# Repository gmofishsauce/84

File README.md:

# Aspirational

**Everything in this repo is aspirational. Nothing has been implemented.**

# Licensing

<br />The content of this repository is licensed under a <a rel="license" href="http://creativecommons.org/licenses/by/4.0/">Creative Commons Attribution 4.0 International License</a>.

# 84CP series

84CP is a series of hardware components for student, experimenter, and hobbyist use. 84CP components are packaged on 3.1" x 1.0" breakout "surfboards". Each component has 60 pins on 0.9" centers with 0.1" traditional (not metric) spacing, allowing one component in a standard 30-pin "small" solderless breadboard or two components in a 64-pin "large" breadboard with one row of breadboard holes open on each side of the component.

The components implement 16-bit slices and include an ALU, 16-bit wide 2:1 multiplexer, registers, controls, random logic, system clock, a VGA adapter, and nonvolatile RAM. 84CP components operate from a 3.3 volt supply, but wide level shifter components are also provided for interfacing with 5 volt logic. All components are designed for use at clock rates up to 10MHz.

Logic components are specializations of AMD Xilinx XC9572XL ("9572") Complex Programmable Logic Device ("CPLD"). A characteristic of CPLDs is that the assignment of functions to pins on the device is performed by the synthesize software, usually leading to arbitrary scrambling of inputs, outputs, control lines, power, and ground. 84CP-series surfboards physically descramble the device pins. Inputs, outputs, and control lines are meaningfully grouped with power and ground at the corners.

The 84CP series is intended for hobbyiest and educational use. All 60 pins protrude upward through the board, making them easily accessible to instrumentation (oscilloscopes and logic analyzers) for debugging and educational use. The pins also allow a single wire wrap directly to the board. Below the board, the pins are long enough for solderless breadboard insertion. Each component includes a top-mount JTAG connector, allowing it to be programmed or reprogrammed at will.

# Planned 84CP series components

- 84CP01 Scrambled baseboard
- 84CP02 Descrambled combinational baseboard with 2 x 16 input, 16 bit output, four control lines, and no clock
- 84CP03 Descrambled clocked baseboard with 16 bit input, 16 bit 3-state output, and multiple control lines
- 84CP04 Descrambled clocked baseboard with 16 bit input, 16 bit output, 16 bit 3-state output, and limited control lines
- 84CP09 Baseboard with 40 MHz clock module and 4-phase 10MHz outputs
- 84CP10 24-bit level shifter with 3 lower-voltage 8-bit enables
- 84CP11 24-bit level shifter with 2 higher-voltage 8-bit enables and 6 always-enabled
- 84CP41 16-bit register unit with 3 registers and five small constants (84CP03 baseboard)
- 84CP42 16 bit register with both 3-state and regular outputs (84CP04 baseboard)
- 84CP71 Four-function ALU with adder (84CP02 baseboard)
- 84CP72 Four-function ALU with subtracter (84CP02 baseboard)
- 84CP73 16 bit 2:1 multiplexer with shifter (84CP02 baseboard)
- 84CP74 ALU flags register and associated logic (similar to 84CP04 baseboard)
- 84CP81 2M x 16 bit nonvolatile static RAM (nonstandard baseboard)
- 84CP91 10MHz 4-phase system clock with 800x600 monochrome VGA adapter (84CP09 baseboard)

# Example 84CP01 Baseboard

# Is the 9572 CPLD obsolete?

The 9572 is a programmable device with up to 72 bits of register storage and more than 1500 equivalent logic gates, not of all which can be used in practice for any particular design. It's available in 44-pin, 64-pin, and 100-pin surface mount packages.

At the cutting edge, CPLD-type devices have been superceded by Field Programmable Gate Arrays (FPGAs) containing enormous amounts of storage and uncommitted logic. Manufacturers prefer to sell denser chips with higher margins, so Xilinx (now AMD Xilinx) has been making efforts to push customers away from the 9572 and its programming software, ISE, for almost a decade.

For a variety of reasons, there has been signficant customer pushback on their efforts.

- CPLDs are signficantly simpler than FPGAs. They had found their way into numerous university engineering programs and are widely used by hobbyists.
- CPLDs use first-generation surface-mount packages like TSOP. Most FPGAs, with their very high external connection counts, are packaged in ball grid and similar packages that are difficult to work with by hand.
- CPLDs are much less expensive than FPGAs. A single 9572 is sufficient to encapsulate many simple logic designs or the entire I/O logic of a fairly complex embedded controller.
- Manufacturers are particularly hesitant to end-of-life programmable components for fear of scaring low- and medium-volume users away from their use in future designs. AMD Xilinx, for example, publicly states that its current FPGA components (such as the Spartan series) will not be end-of-lifed until at least 2035.

No end of life announcement for the 9572 has been made and it's available from all large electronics distributers from under $10 US.

But the second (and mandatory) ingredient of any programmable device is the programming software. Despite some efforts in the open source community, Xilinx' proprietary ISE software remains the only full-function solution for the 9572. The ISE programming software is no longer maintained; Xilinx has moved all development to its Vivado software, which does not support the 9572. This is a completely understandable business decision given the enormous complexity of such software.

During the 20-teens, Xilinx stopped providing ISE upgrades for recent versions of Windows and crippled the Linux version of the software. Xilinx' efforts to push customers away from CPLDs have led to a huge amount of misinformation on the internet. Another result was significant customer pushback, which eventually caused them to quietly back off from their position.

Eventually, Xilinx released a fully-functional version of the ISE software in a Linux virtual machine. The VM can be used with Oracle VirtualBox, which runs the VM and its now-obsolete version of Linux on a host network that is completely disconnected from the internet. This makes it, in my opinion, reasonably safe for use on a NATted LAN.

So that's the bottom line. The part exists and is still being manufactured. The software exists in a fully-encapsulated and isolated form. It's enough for me, as a hobbyiest, to move on with the part.

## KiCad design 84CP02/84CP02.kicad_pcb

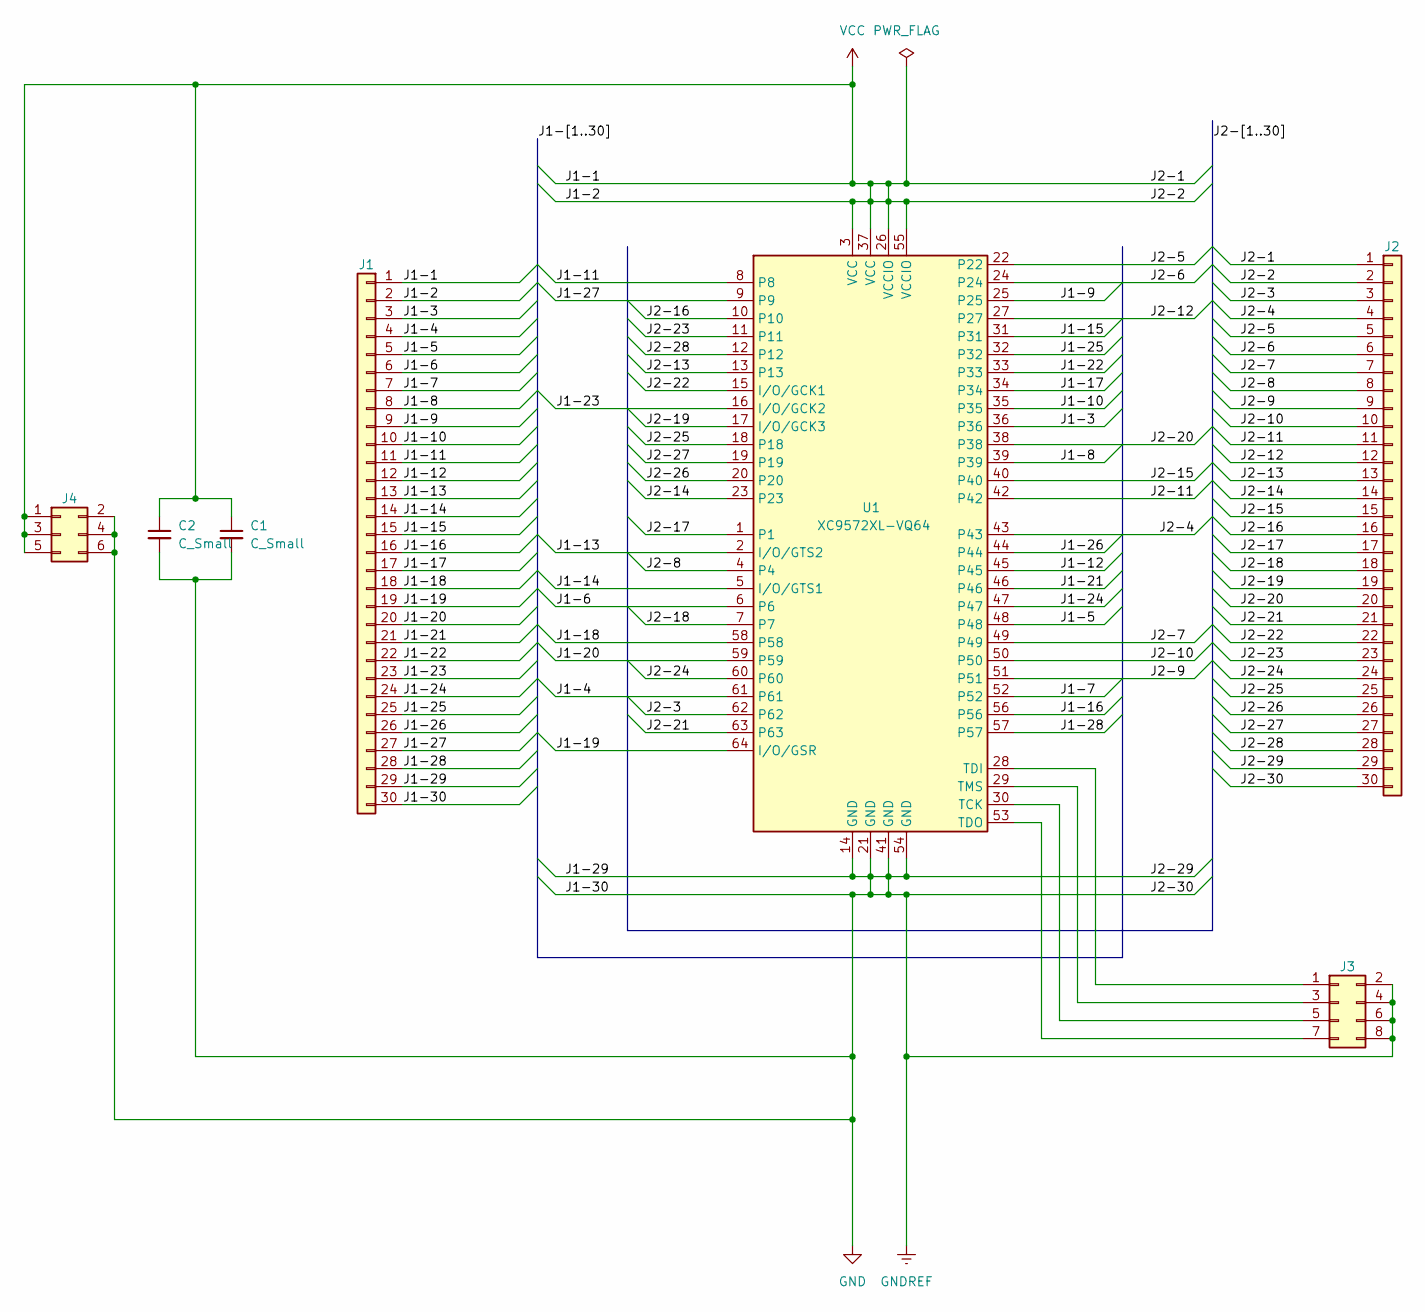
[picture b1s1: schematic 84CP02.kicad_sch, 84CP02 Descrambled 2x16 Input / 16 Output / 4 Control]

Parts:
C1, C2: C_Small; C_0805_2012Metric_Pad1.18x1.45mm_HandSolder
J1, J2: Conn_01x30; PinHeader_1x30_P2.54mm_Vertical
J3: Conn_02x05_Odd_Even; PinHeader_2x04_P2.54mm_Vertical
J4: Conn_02x03_Odd_Even; PinHeader_2x03_P2.54mm_Vertical
U1: XC9572XL-VQ64; TQFP-64_10x10mm_P0.5mm

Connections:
/J1-3: J1.3, U1.36
/J1-4: J1.4, U1.61
/J1-5: J1.5, U1.48
/J1-6: J1.6, U1.6
/J1-7: J1.7, U1.52
/J1-8: J1.8, U1.39
/J1-9: J1.9, U1.25
/J1-10: J1.10, U1.35
/J1-11: J1.11, U1.8
/J1-12: J1.12, U1.45
/J1-13: J1.13, U1.2 (I/O/GTS2)
/J1-14: J1.14, U1.5 (I/O/GTS1)
/J1-15: J1.15, U1.31
/J1-16: J1.16, U1.56
/J1-17: J1.17, U1.34
/J1-18: J1.18, U1.58
/J1-19: J1.19, U1.64 (I/O/GSR)
/J1-20: J1.20, U1.59
/J1-21: J1.21, U1.46
/J1-22: J1.22, U1.33
/J1-23: J1.23, U1.16 (I/O/GCK2)
/J1-24: J1.24, U1.47
/J1-25: J1.25, U1.32
/J1-26: J1.26, U1.44
/J1-27: J1.27, U1.9
/J1-28: J1.28, U1.57
/J2-3: J2.3, U1.62
/J2-4: J2.4, U1.43
/J2-5: J2.5, U1.22
/J2-6: J2.6, U1.24
/J2-7: J2.7, U1.49
/J2-8: J2.8, U1.4
/J2-9: J2.9, U1.51
/J2-10: J2.10, U1.50
/J2-11: J2.11, U1.42
/J2-12: J2.12, U1.27
/J2-13: J2.13, U1.13
/J2-14: J2.14, U1.23
/J2-15: J2.15, U1.40
/J2-16: J2.16, U1.10
/J2-17: J2.17, U1.1
/J2-18: J2.18, U1.7
/J2-19: J2.19, U1.17 (I/O/GCK3)
/J2-20: J2.20, U1.38
/J2-21: J2.21, U1.63
/J2-22: J2.22, U1.15 (I/O/GCK1)
/J2-23: J2.23, U1.11
/J2-24: J2.24, U1.60
/J2-25: J2.25, U1.18
/J2-26: J2.26, U1.20
/J2-27: J2.27, U1.19
/J2-28: J2.28, U1.12
GND: C1.2, C2.2, J1.29, J1.30, J2.29, J2.30, J3.2, J3.4, J3.6, J3.8, J4.2, J4.4, J4.6, U1.14 (GND), U1.21 (GND), U1.41 (GND), U1.54 (GND)
unnamed: J3.1, U1.28 (TDI)
unnamed: J3.3, U1.29 (TMS)
unnamed: J3.5, U1.30 (TCK)
unnamed: J3.7, U1.53 (TDO)
VCC: C1.1, C2.1, J1.1, J1.2, J2.1, J2.2, J4.1, J4.3, J4.5, U1.3 (VCC), U1.26 (VCCIO), U1.37 (VCC), U1.55 (VCCIO)

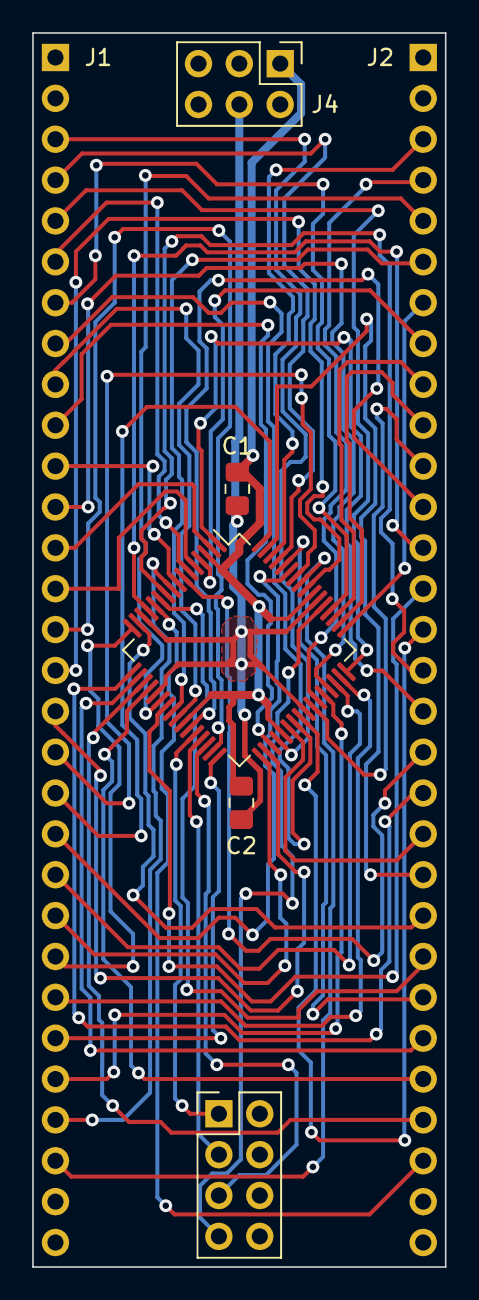
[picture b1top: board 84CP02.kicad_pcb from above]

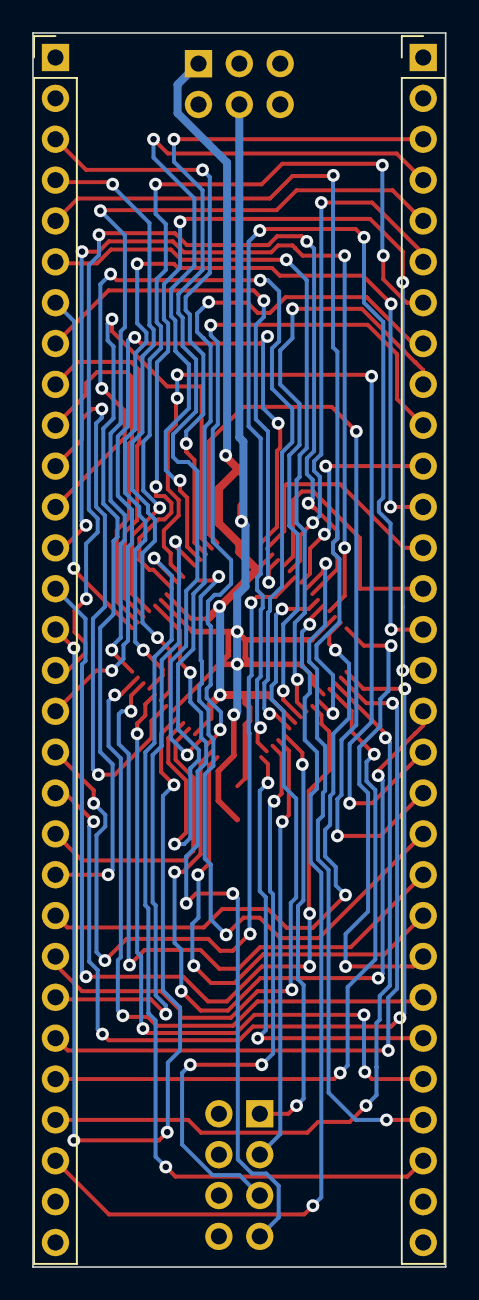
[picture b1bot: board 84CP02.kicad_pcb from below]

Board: 4 copper layers, 25.7 x 76.7 mm, 7 parts (2 on the bottom side), 58 nets.

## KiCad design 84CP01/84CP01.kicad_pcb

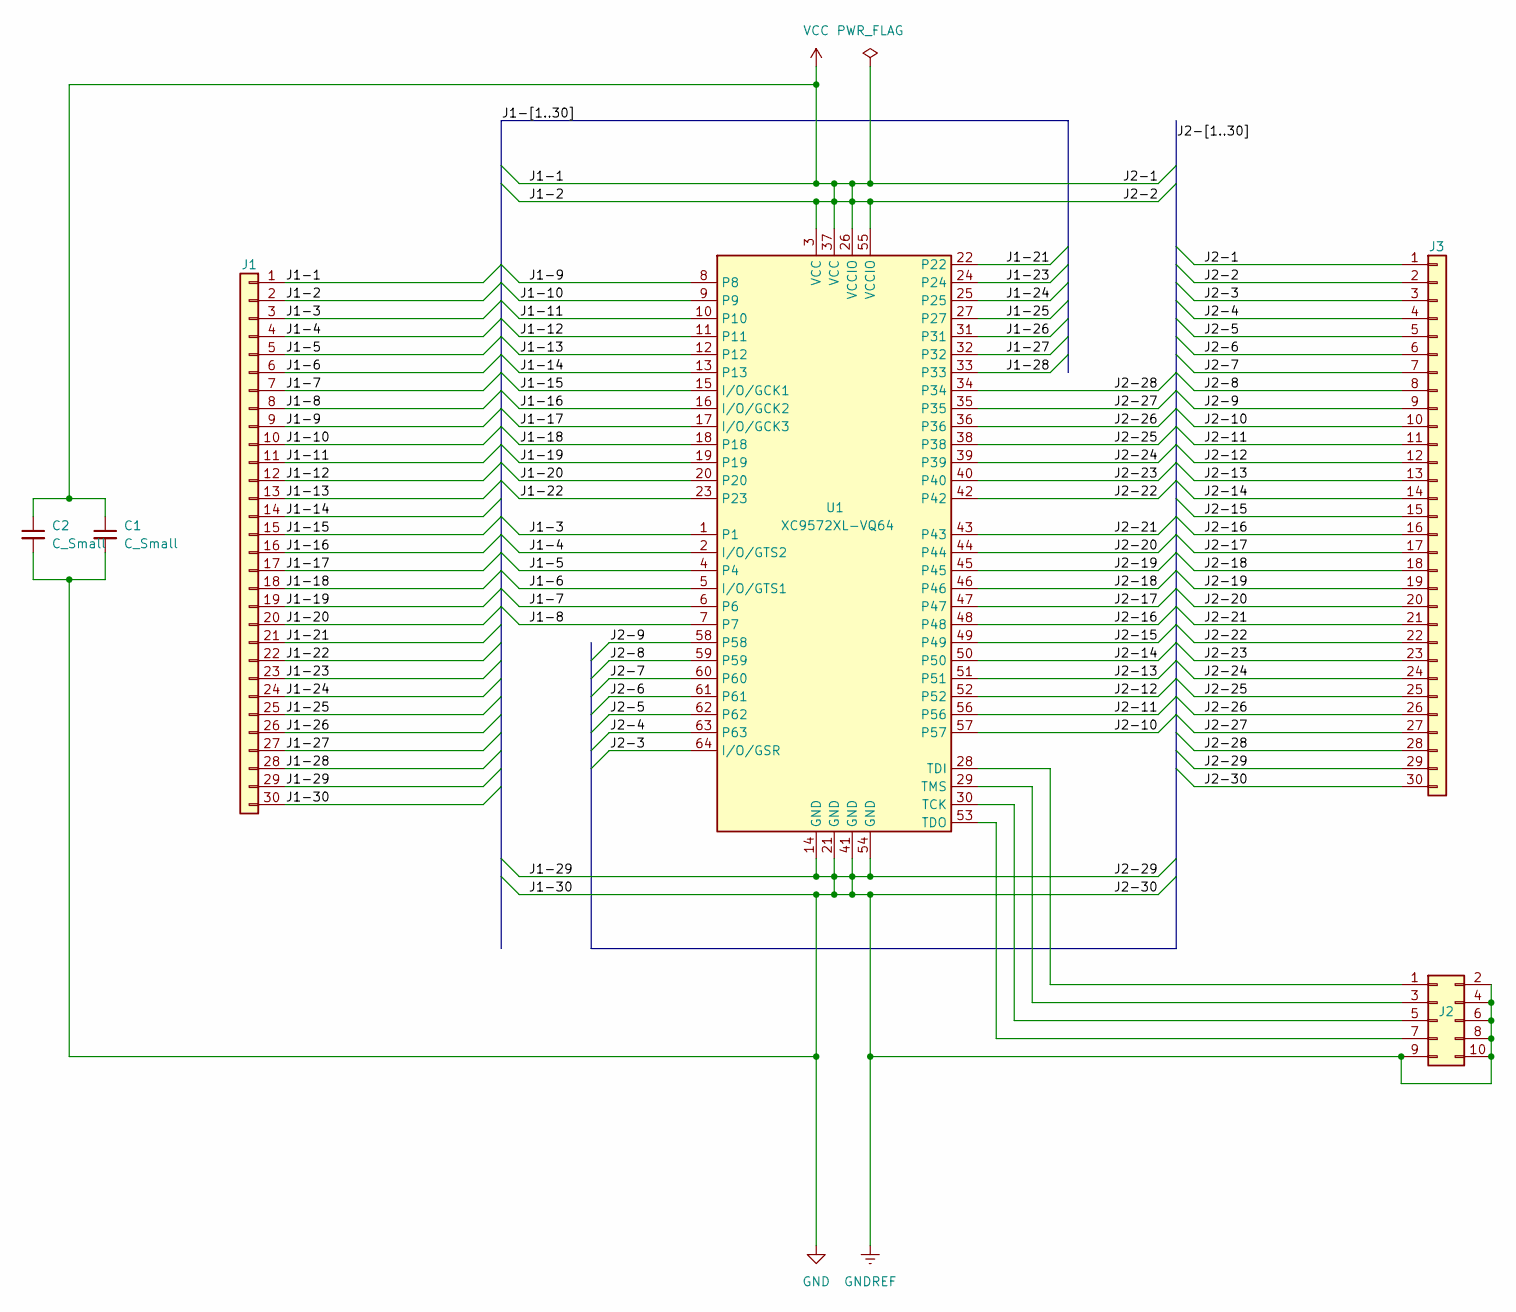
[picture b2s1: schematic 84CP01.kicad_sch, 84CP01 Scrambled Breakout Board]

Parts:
C1, C2: C_Small; C_0805_2012Metric_Pad1.18x1.45mm_HandSolder
J1, J3: Conn_01x30; PinHeader_1x30_P2.54mm_Vertical
J2: Conn_02x05_Odd_Even; Molex_Nano-Fit_105310-xx10_2x05_P2.50mm_Vertical
U1: XC9572XL-VQ64; TQFP-64_10x10mm_P0.5mm

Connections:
/J1-3: J1.3, U1.1
/J1-4: J1.4, U1.2 (I/O/GTS2)
/J1-5: J1.5, U1.4
/J1-6: J1.6, U1.5 (I/O/GTS1)
/J1-7: J1.7, U1.6
/J1-8: J1.8, U1.7
/J1-9: J1.9, U1.8
/J1-10: J1.10, U1.9
/J1-11: J1.11, U1.10
/J1-12: J1.12, U1.11
/J1-13: J1.13, U1.12
/J1-14: J1.14, U1.13
/J1-15: J1.15, U1.15 (I/O/GCK1)
/J1-16: J1.16, U1.16 (I/O/GCK2)
/J1-17: J1.17, U1.17 (I/O/GCK3)
/J1-18: J1.18, U1.18
/J1-19: J1.19, U1.19
/J1-20: J1.20, U1.20
/J1-21: J1.21, U1.22
/J1-22: J1.22, U1.23
/J1-23: J1.23, U1.24
/J1-24: J1.24, U1.25
/J1-25: J1.25, U1.27
/J1-26: J1.26, U1.31
/J1-27: J1.27, U1.32
/J1-28: J1.28, U1.33
/J2-3: J3.3, U1.64 (I/O/GSR)
/J2-4: J3.4, U1.63
/J2-5: J3.5, U1.62
/J2-6: J3.6, U1.61
/J2-7: J3.7, U1.60
/J2-8: J3.8, U1.59
/J2-9: J3.9, U1.58
/J2-10: J3.10, U1.57
/J2-11: J3.11, U1.56
/J2-12: J3.12, U1.52
/J2-13: J3.13, U1.51
/J2-14: J3.14, U1.50
/J2-15: J3.15, U1.49
/J2-16: J3.16, U1.48
/J2-17: J3.17, U1.47
/J2-18: J3.18, U1.46
/J2-19: J3.19, U1.45
/J2-20: J3.20, U1.44
/J2-21: J3.21, U1.43
/J2-22: J3.22, U1.42
/J2-23: J3.23, U1.40
/J2-24: J3.24, U1.39
/J2-25: J3.25, U1.38
/J2-26: J3.26, U1.36
/J2-27: J3.27, U1.35
/J2-28: J3.28, U1.34
GND: C1.2, C2.2, J1.29, J1.30, J2.2, J2.4, J2.6, J2.8, J2.9, J2.10, J3.29, J3.30, U1.14 (GND), U1.21 (GND), U1.41 (GND), U1.54 (GND)
unnamed: J2.1, U1.28 (TDI)
unnamed: J2.3, U1.29 (TMS)
unnamed: J2.5, U1.30 (TCK)
unnamed: J2.7, U1.53 (TDO)
VCC: C1.1, C2.1, J1.1, J1.2, J3.1, J3.2, U1.3 (VCC), U1.26 (VCCIO), U1.37 (VCC), U1.55 (VCCIO)

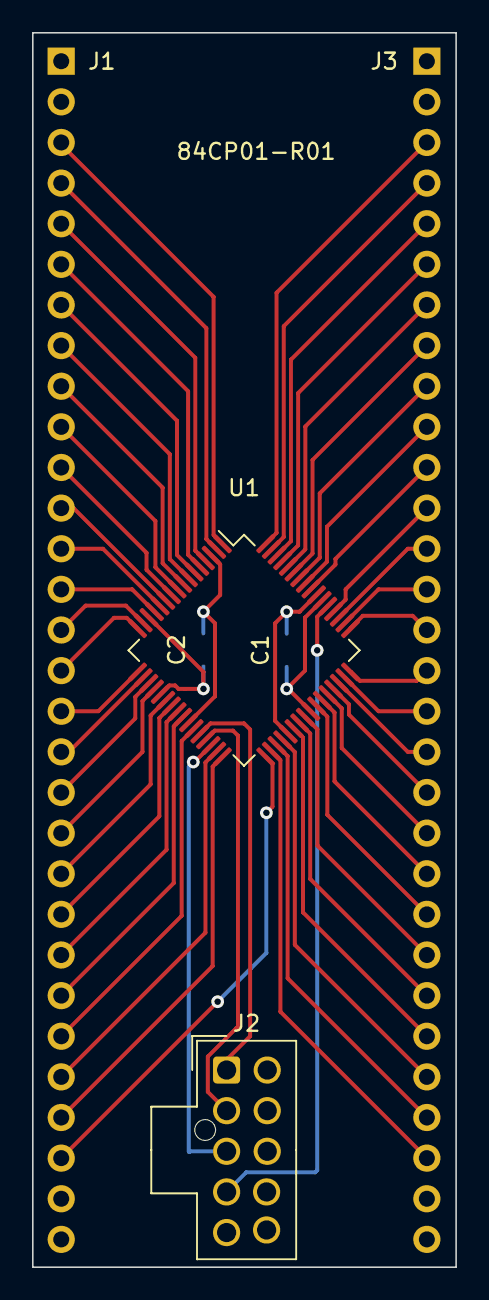
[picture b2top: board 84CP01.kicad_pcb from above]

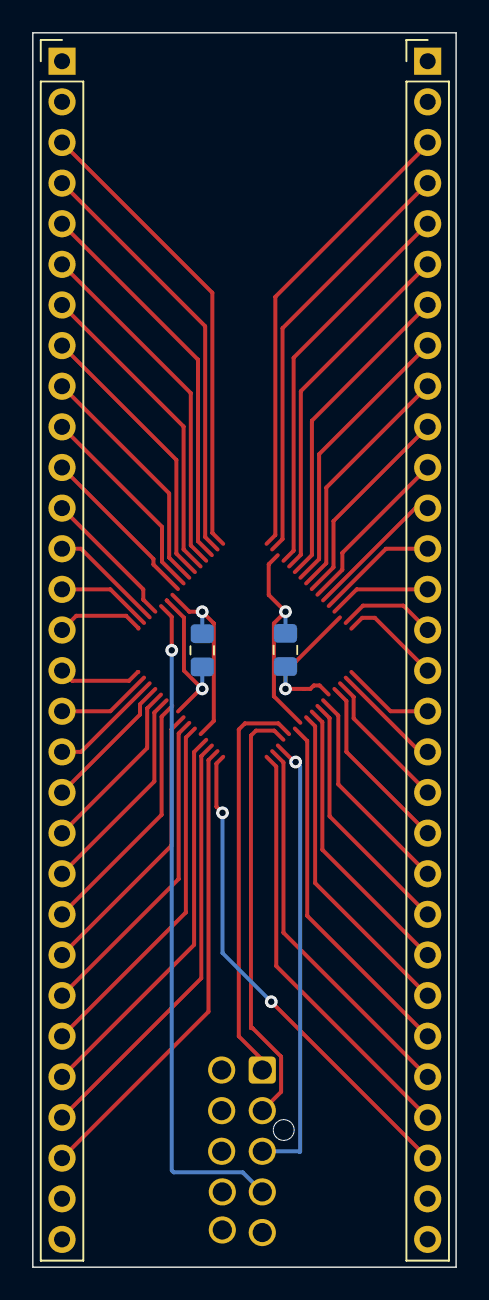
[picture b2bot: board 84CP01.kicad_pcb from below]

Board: 4 copper layers, 26.5 x 77.2 mm, 6 parts (4 on the bottom side), 58 nets.

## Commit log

2023-07-17 Update README with aspirational goals
2023-07-17 Attempt to include HTML in README.md
2023-07-17 Update suitability statement
2023-07-18 84CP01-R01 layout
2023-07-18 Produce Gerbers for fabrication
2023-07-19 Move image file to a more convenient location
2023-07-20 Drill files for PCB layout
2023-07-20 84CP02 in progress
2023-07-20 Again revise pin mapping table
2023-07-20 Continuing development
2023-07-20 Add a minimal backup of Verilog while I work out file sharing with the VM that runs ISE
2023-07-20 Add Verilog for 4-function ALU chip
2023-07-21 Ongoing Verilog development
2023-07-21 Implement pin locking and confirmed that it works on subtractor chip. This is an important milestone that makes possible the baseboard approach.
2023-07-22 First attempts at routing the CP02 baseboard
2023-07-23 Ongoing routing
2023-07-23 Tagging this commit as failed_routing_1 before backing out and trying a different approach.
2023-07-25 84CP02 board is routed and all DRC errors and warnings are fixed.
2023-07-25 A few polishing changes and rerun the Design Rule Checker
2023-12-23 commit Gerbers for this project
